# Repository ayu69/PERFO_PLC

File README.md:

# PERFO_PLC

Vous trouverez l'ensemble des schémas et routage des cartes

Bus Fond de panier :

CPU :

Carte Entrée :

Carte Sorties :

Perfo PLC

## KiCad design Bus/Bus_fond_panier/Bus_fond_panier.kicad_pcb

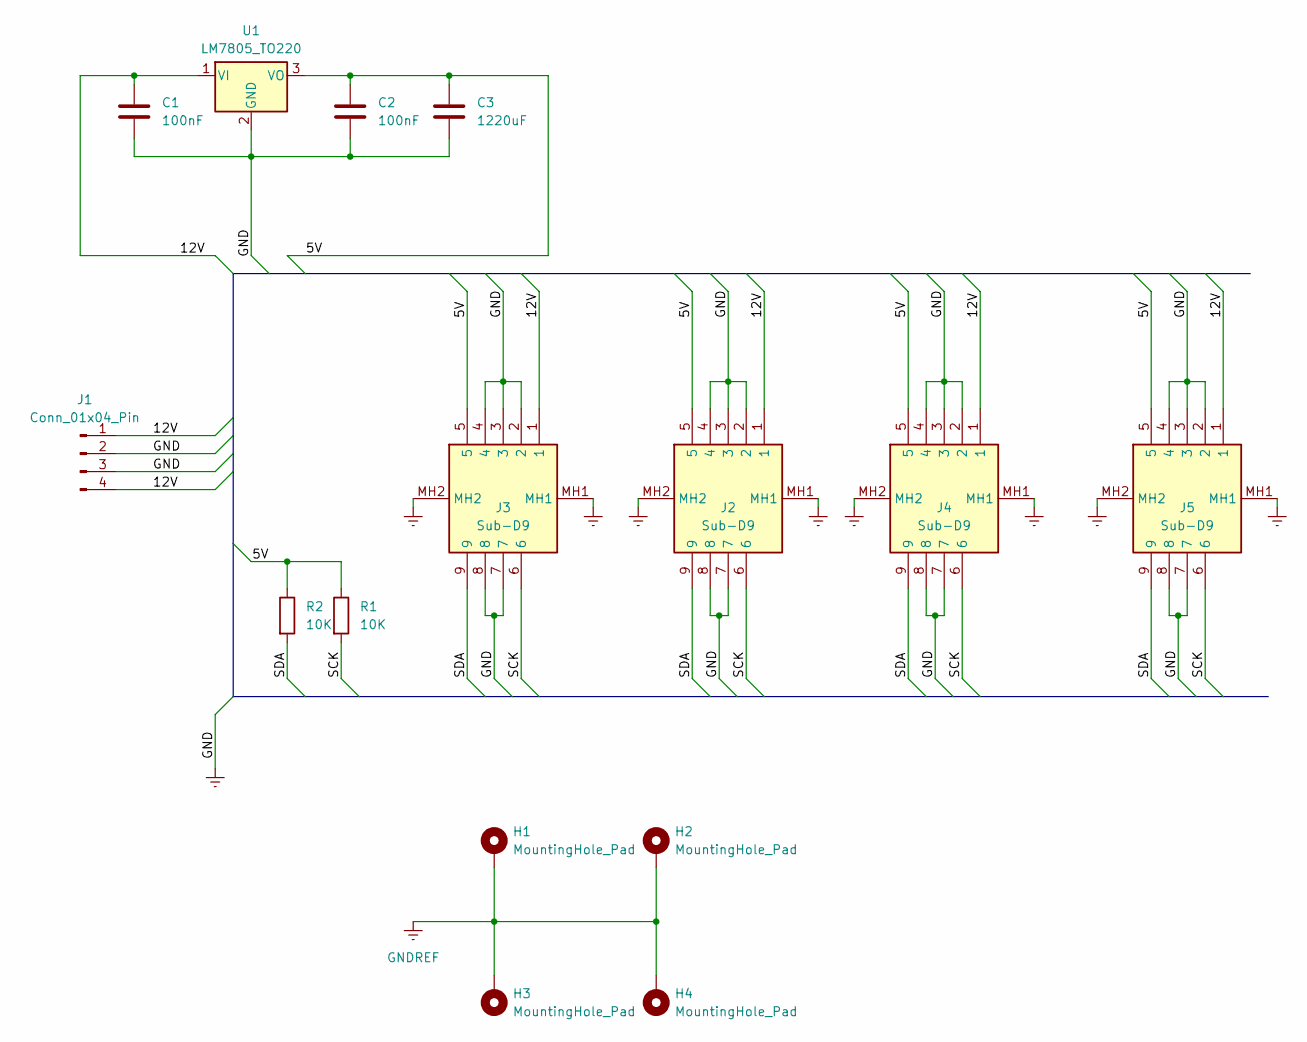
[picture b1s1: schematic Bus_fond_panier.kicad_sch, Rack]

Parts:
C1, C2: 100nF; C_Radial_D4.0mm_H7.0mm_P1.50mm
C3: 1220uF; C_Radial_D4.0mm_H7.0mm_P1.50mm
H1, H2, H3, H4: MountingHole_Pad; MountingHole_3.2mm_M3_Pad_Via
J1: Conn_01x04_Pin; JST_EH_S4B-EH_1x04_P2.50mm_Horizontal
J2, J3, J4, J5: Sub-D9; NFD17E09SAFC1DA; Manufacturer_Part_Number NFD17E09SAFC1DA
R1, R2: 10K; R_Axial_DIN0207_L6.3mm_D2.5mm_P10.16mm_Horizontal
U1: LM7805_TO220; TO-220-3_Vertical

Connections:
/5V: C2.1, C3.1, J2.5, J3.5, J4.5, J5.5, R1.1, R2.1, U1.3 (VO)
/12V: C1.1, J1.1, J1.4, J2.1, J3.1, J4.1, J5.1, U1.1 (VI)
/SCK: J2.6, J3.6, J4.6, J5.6, R1.2
/SDA: J2.9, J3.9, J4.9, J5.9, R2.2
GNDREF: C1.2, C2.2, C3.2, H1.1, H2.1, H3.1, H4.1, J1.2, J1.3, J2.2, J2.3, J2.4, J2.7, J2.8, J2.MH1, J2.MH2, J3.2, J3.3, J3.4, J3.7, J3.8, J3.MH1, J3.MH2, J4.2, J4.3, J4.4, J4.7, J4.8, J4.MH1, J4.MH2, J5.2, J5.3, J5.4, J5.7, J5.8, J5.MH1, J5.MH2, U1.2 (GND)

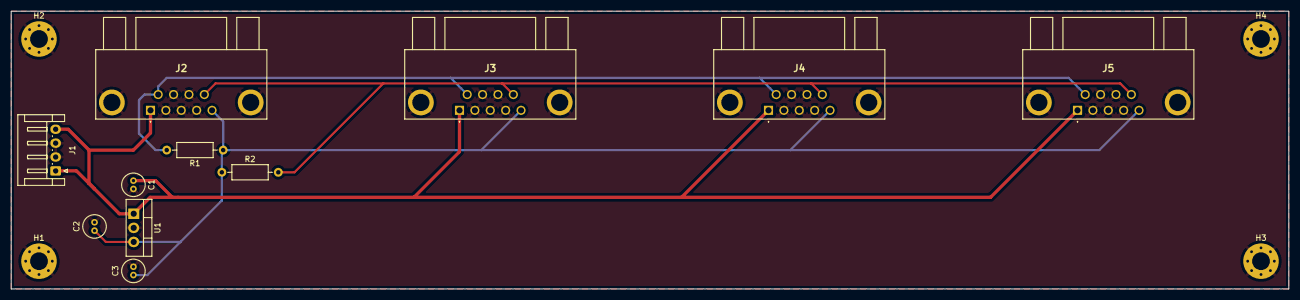
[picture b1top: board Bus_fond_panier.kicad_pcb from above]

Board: 2 copper layers, 230.0 x 50.0 mm, 15 parts (0 on the bottom side), 5 nets.

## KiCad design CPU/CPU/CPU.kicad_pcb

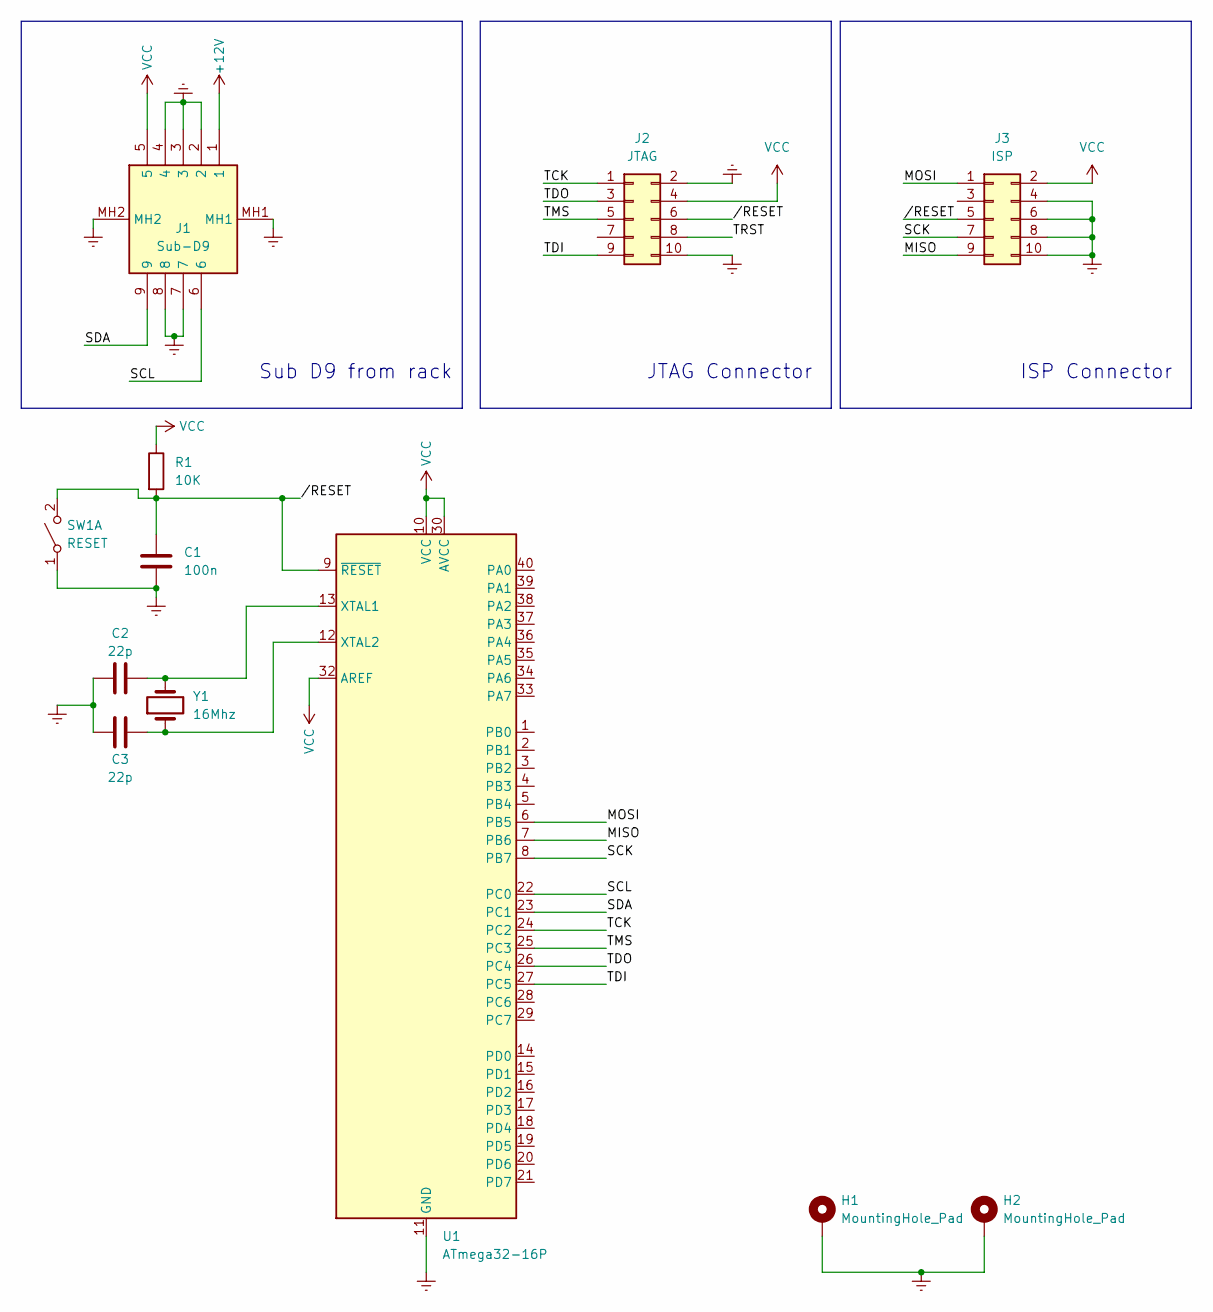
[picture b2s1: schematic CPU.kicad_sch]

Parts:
C1: 100n; C_Radial_D4.0mm_H5.0mm_P1.50mm
C2, C3: 22p; C_Radial_D4.0mm_H5.0mm_P1.50mm
H1, H2: MountingHole_Pad; MountingHole_3.2mm_M3_Pad_Via
J1: Sub-D9; NFD17E09SAFC1DA; Manufacturer_Part_Number NFD17E09SAFC1DA
J2: JTAG; IDC-Header_2x05_P2.54mm_Vertical
J3: ISP; IDC-Header_2x05_P2.54mm_Vertical
R1: 10K; R_Axial_DIN0207_L6.3mm_D2.5mm_P10.16mm_Horizontal
SW1: RESET; PTS645SH952LFS
U1: ATmega32-16P; DIP-40_W15.24mm
Y1: 16Mhz; Crystal_HC49-4H_Vertical

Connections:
+12V: J1.1
/MISO: J3.9, U1.7 (PB6)
/MOSI: J3.1, U1.6 (PB5)
/SCK: J3.7, U1.8 (PB7)
/SCL: J1.6, U1.22 (PC0)
/SDA: J1.9, U1.23 (PC1)
/TCK: J2.1, U1.24 (PC2)
/TDI: J2.9, U1.27 (PC5)
/TDO: J2.3, U1.26 (PC4)
/TMS: J2.5, U1.25 (PC3)
/TRST: J2.8
//RESET: C1.1, J2.6, J3.5, R1.2, SW1.2 (B), U1.9 (~RESET)
GNDREF: C1.2, C2.1, C3.1, H1.1, H2.1, J1.2, J1.3, J1.4, J1.7, J1.8, J1.MH1, J1.MH2, J2.2, J2.10, J3.4, J3.6, J3.8, J3.10, SW1.1 (A), U1.11 (GND), U1.31 (GND)
unnamed: C2.2, U1.13 (XTAL1), Y1.2
unnamed: C3.2, U1.12 (XTAL2), Y1.1
VCC: J1.5, J2.4, J3.2, R1.1, U1.10 (VCC), U1.30 (AVCC), U1.32 (AREF)

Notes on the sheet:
JTAG Connector
Sub D9 from rack
ISP Connector

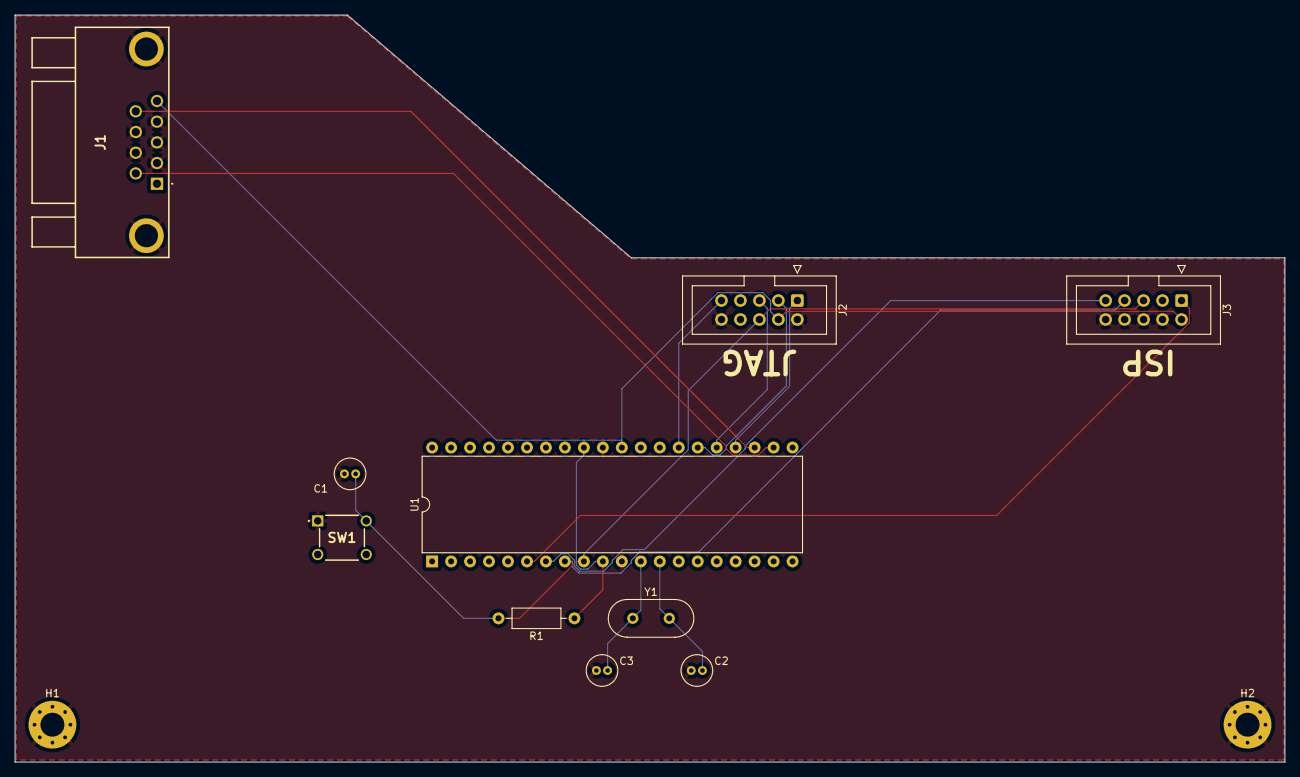
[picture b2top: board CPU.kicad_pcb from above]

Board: 2 copper layers, 170.0 x 100.0 mm, 12 parts (0 on the bottom side), 14 nets.

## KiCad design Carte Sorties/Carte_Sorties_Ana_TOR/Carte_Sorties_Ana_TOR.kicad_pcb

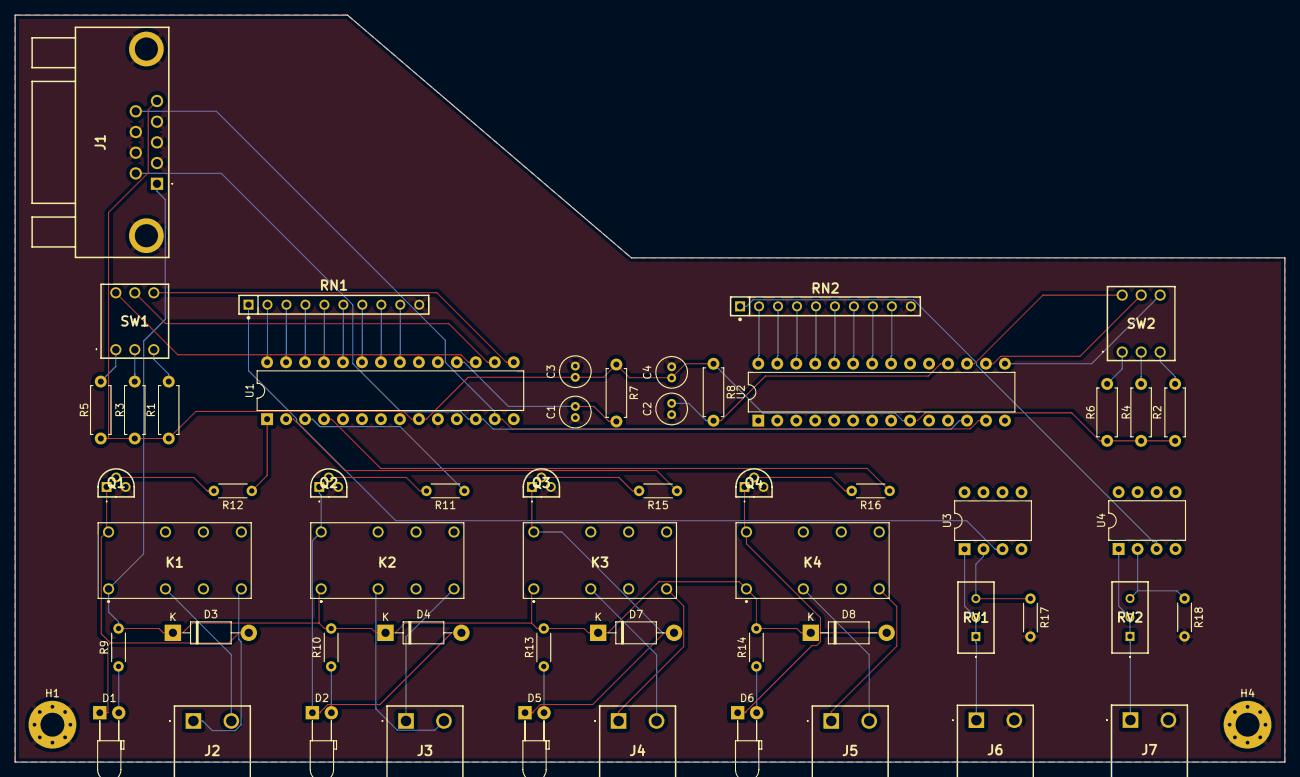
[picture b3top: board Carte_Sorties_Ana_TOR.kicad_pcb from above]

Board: 2 copper layers, 170.0 x 100.0 mm, 57 parts (0 on the bottom side), 65 nets.

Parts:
C1, C2, C3, C4: 100nF; C_Radial_D4.0mm_H5.0mm_P1.50mm
D1, D2, D5, D6: LED; LED_D3.0mm_Horizontal_O3.81mm_Z6.0mm
D3, D4, D7, D8: 1N4007; D_DO-41_SOD81_P10.16mm_Horizontal
H1, H4: MountingHole_Pad; MountingHole_3.2mm_M3_Pad_Via
J1: Sub-D9; NFD17E09SAFC1DA
J2, J6, J7: Out_1; 1735882
J3: Out_3; 1735882
J4: Out_2; 1735882
J5: Out_4; 1735882
K1, K2, K3, K4: G5V-2-DC12; G5V23DC
Q1, Q2, Q3, Q4: 2N3417 PBFREE; 2N3417PBFREE
R1, R2, R3, R4, R5, R6, R7, R8: 10K; R_Axial_DIN0207_L6.3mm_D2.5mm_P7.62mm_Horizontal
R9, R10, R13, R14: 330; R_Axial_DIN0204_L3.6mm_D1.6mm_P5.08mm_Horizontal
R11, R12, R15, R16: 1K; R_Axial_DIN0204_L3.6mm_D1.6mm_P5.08mm_Horizontal
R17, R18: 10K; R_Axial_DIN0204_L3.6mm_D1.6mm_P5.08mm_Horizontal
RN1, RN2: 4610X-R2R-103LF; SIP249W51P254L2535H508Q10P
RV1, RV2: 22K; 3296W1223LF
SW1, SW2: DS01C-254-S-03BE; DS01C254S03BE
U1, U2: MCP23017_SP; DIP-28_W7.62mm
U3, U4: TL074; DIP-8_W7.62mm

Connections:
+12V: D3.1 (K), D4.1 (K), D7.1 (K), D8.1 (K), J1.1, K1.1, K2.1, K3.1, K4.1, R9.2, R10.2, R13.2, R14.2
/SCK: J1.6, U1.12 (SCK), U2.12 (SCK)
/SDA: J1.9, U1.13 (SDA), U2.13 (SDA)
Ana_1_Out_0: RN1.9, U1.21 (GPA0)
Ana_1_Out_1: RN1.8, U1.22 (GPA1)
Ana_1_Out_2: RN1.7, U1.23 (GPA2)
Ana_1_Out_3: RN1.6, U1.24 (GPA3)
Ana_1_Out_4: RN1.5, U1.25 (GPA4)
Ana_1_Out_5: RN1.4, U1.26 (GPA5)
Ana_1_Out_6: RN1.3, U1.27 (GPA6)
Ana_1_Out_7: RN1.2, U1.28 (GPA7)
Ana_2_Out_0: RN2.9, U2.21 (GPA0)
Ana_2_Out_1: RN2.8, U2.22 (GPA1)
Ana_2_Out_2: RN2.7, U2.23 (GPA2)
Ana_2_Out_3: RN2.6, U2.24 (GPA3)
Ana_2_Out_4: RN2.5, U2.25 (GPA4)
Ana_2_Out_5: RN2.4, U2.26 (GPA5)
Ana_2_Out_6: RN2.3, U2.27 (GPA6)
Ana_2_Out_7: RN2.2, U2.28 (GPA7)
GNDREF: C1.1, C2.1, C3.2, C4.2, H1.1, H4.1, J1.2, J1.3, J1.4, J1.7, J1.8, J1.MH1, J1.MH2, J6.2, J7.2, Q1.3 (E), Q2.3 (E), Q3.3 (E), Q4.3 (E), R17.2, R18.2, RN1.10, RN2.10, U1.10 (VSS), U2.10 (VSS)
unnamed: D1.2 (A), R9.1
unnamed: D1.1 (K), D3.2 (A), K1.16, Q1.1 (C)
unnamed: D2.2 (A), R10.1
unnamed: D2.1 (K), D4.2 (A), K2.16, Q2.1 (C)
unnamed: D5.2 (A), R13.1
unnamed: D5.1 (K), D7.2 (A), K3.16, Q3.1 (C)
unnamed: D6.2 (A), R14.1
unnamed: D6.1 (K), D8.2 (A), K4.16, Q4.1 (C)
unnamed: J2.1, K1.8
unnamed: J2.2, K1.4
unnamed: J3.1, K2.8
unnamed: J3.2, K2.4
unnamed: J4.1, K3.8
unnamed: J4.2, K3.4
unnamed: J5.1, K4.8
unnamed: J5.2, K4.4
unnamed: J6.1, RV1.1, RV1.2, U3.1
unnamed: J7.1, RV2.1, RV2.2, U4.1
unnamed: Q1.2 (B), R12.2
unnamed: Q2.2 (B), R11.2
unnamed: Q3.2 (B), R15.2
unnamed: Q4.2 (B), R16.2
unnamed: R1.2, SW1.5
unnamed: R2.2, SW2.5
unnamed: R3.2, SW1.3
unnamed: R4.2, SW2.3
unnamed: R5.1, SW1.1
unnamed: R6.1, SW2.1
unnamed: SW1.6, U1.15 (A0)
unnamed: SW1.4, U1.16 (A1)
unnamed: SW1.2, U1.17 (A2)
unnamed: C1.2, R7.2, U1.18 (~RESET)
unnamed: SW2.6, U2.15 (A0)
unnamed: SW2.4, U2.16 (A1)
unnamed: SW2.2, U2.17 (A2)
unnamed: C2.2, R8.2, U2.18 (~RESET)
unnamed: RN1.1, U3.3 (+)
unnamed: R17.1, RV1.3, U3.2 (-)
unnamed: RN2.1, U4.3 (+)
unnamed: R18.1, RV2.3, U4.2 (-)
Tor_Out_1: R12.1, U1.1 (GPB0)
Tor_Out_2: R15.1, U1.2 (GPB1)
Tor_Out_3: R11.1, U1.3 (GPB2)
Tor_Out_4: R16.1, U1.4 (GPB3)
VCC: C3.1, C4.1, J1.5, R1.1, R2.1, R3.1, R4.1, R5.2, R6.2, R7.1, R8.1, U1.9 (VDD), U2.9 (VDD)

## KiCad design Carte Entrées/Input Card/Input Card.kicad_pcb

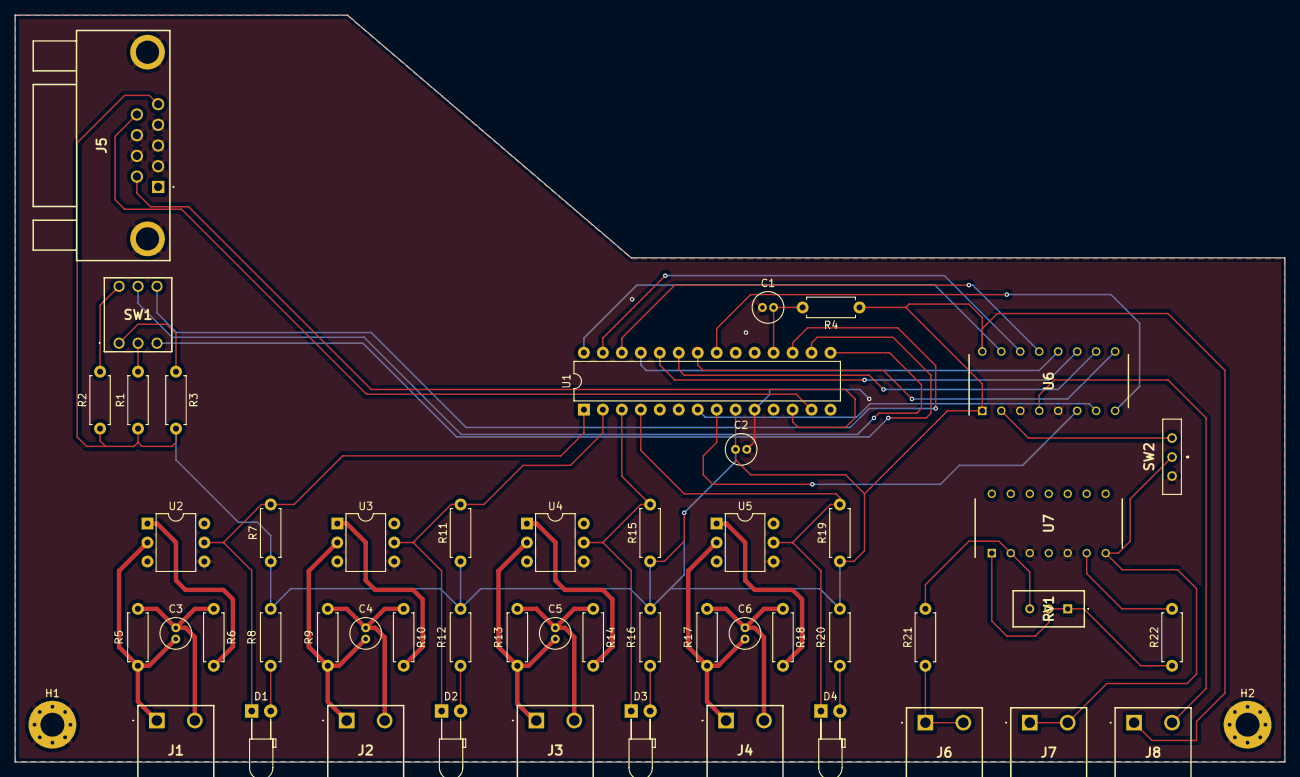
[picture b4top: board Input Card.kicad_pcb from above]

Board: 2 copper layers, 170.0 x 100.0 mm, 52 parts (0 on the bottom side), 48 nets.

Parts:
C1, C2: 100nF; C_Radial_D4.0mm_H5.0mm_P1.50mm
C3, C4, C5, C6: C; C_Radial_D4.0mm_H5.0mm_P1.50mm
D1, D2, D3, D4: LED; LED_D3.0mm_Horizontal_O3.81mm_Z2.0mm
H1, H2: MountHole; MountingHole_3.2mm_M3_Pad_Via
J1, J2, J3, J4, J6, J7, J8: Screw_Terminal_01x02; 1735882
J5: Sub-D9; NFD17E09SAFC1DA
R1, R2, R3, R4, R21: 10K; R_Axial_DIN0207_L6.3mm_D2.5mm_P7.62mm_Horizontal
R5, R6, R7, R9, R10, R11, R13, R14, R15, R17, R18, R19: R; R_Axial_DIN0207_L6.3mm_D2.5mm_P7.62mm_Horizontal
R8, R12, R16, R20: 100; R_Axial_DIN0207_L6.3mm_D2.5mm_P7.62mm_Horizontal
R22: 33K; R_Axial_DIN0207_L6.3mm_D2.5mm_P7.62mm_Horizontal
RV1: 10K; 3296W1223LF
SW1: DS01C-254-S-03BE; DS01C254S03BE
SW2: SW_DPDT_x2; 090329001
U1: MCP23017_SP; DIP-28_W7.62mm
U2, U3, U4, U5: 4N25; DIP-6_W7.62mm
U6: AD7819; DIP794W56P254L2013H533Q16N
U7: TL084; DIP794W53P254L1930H508Q14N

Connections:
/GNDREF_1: C3.2, J1.1, R5.2, U2.2
/GNDREF_2: C4.2, J2.1, R9.2, U3.2
/GNDREF_3: C5.2, J3.1, R13.2, U4.2
/GNDREF_4: C6.2, J4.1, R17.2, U5.2
/SCK: J5.6, U1.12 (SCK)
/SDA: J5.9, U1.13 (SDA)
CAN0: U1.21 (GPA0), U6.8 (DB0)
CAN1: U1.22 (GPA1), U6.9 (DB1)
CAN2: U1.23 (GPA2), U6.10 (DB2)
CAN3: U1.24 (GPA3), U6.11 (DB3)
CAN4: U1.25 (GPA4), U6.12 (DB4)
CAN5: U1.26 (GPA5), U6.13 (DB5)
CAN6: U1.27 (GPA6), U6.14 (DB6)
CAN7: U1.28 (GPA7), U6.15 (DB7)
GNDREF: C1.1, C2.2, H1.1, H2.1, J5.2, J5.3, J5.4, J5.7, J5.8, J5.MH1, J5.MH2, SW2.3 (C), U1.10 (VSS), U2.4, U3.4, U4.4, U5.4, U6.3 (GND), U6.5 (CS), U7.3 (+), U7.5 (+)
unnamed: D1.2 (A), R8.2
unnamed: D2.2 (A), R12.2
unnamed: D3.2 (A), R16.2
unnamed: D4.2 (A), R20.2
unnamed: C3.1, J1.2, R5.1, R6.1
unnamed: C4.1, J2.2, R9.1, R10.1
unnamed: C5.1, J3.2, R13.1, R14.1
unnamed: C6.1, J4.2, R17.1, R18.1
unnamed: J6.1, J6.2, R21.1
unnamed: J7.1, J7.2, SW2.1 (A), U7.7
unnamed: J8.2, U6.4 (START)
unnamed: R1.2, SW1.3
unnamed: R2.2, SW1.2
unnamed: R3.1, SW1.1
unnamed: R6.2, U2.1
unnamed: R10.2, U3.1
unnamed: R14.2, U4.1
unnamed: R18.2, U5.1
unnamed: R22.1, RV1.1, RV1.2, U7.1
unnamed: SW2.2 (B), U6.2 (Vin)
unnamed: SW1.4, U1.15 (A0)
unnamed: SW1.5, U1.16 (A1)
unnamed: SW1.6, U1.17 (A2)
unnamed: C1.2, R4.2, U1.18 (~RESET)
unnamed: R21.2, RV1.3, U7.2 (-)
unnamed: R22.2, U7.6 (-)
Read_CAN: U1.8 (GPB7), U6.6 (OE)
Read_Ok: U1.7 (GPB6), U6.7 (EOC)
TOR_Input0: D1.1 (K), R7.2, U1.1 (GPB0), U2.5
TOR_Input1: D2.1 (K), R11.2, U1.2 (GPB1), U3.5
TOR_Input2: D3.1 (K), R15.2, U1.3 (GPB2), U4.5
TOR_Input3: D4.1 (K), R19.2, U1.4 (GPB3), U5.5
VCC: C2.1, J5.5, J8.1, R1.1, R2.1, R3.2, R4.1, R7.1, R8.1, R11.1, R12.1, R15.1, R16.1, R19.1, R20.1, U1.9 (VDD), U6.1 (VREF), U6.16 (VCC)
